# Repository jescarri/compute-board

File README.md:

# compute-board

This project is part of a template ecosystem for generating add-ons for my
custom esp32-powered compute boards.

It expects a 4-layer PCB with controlled impedance to 50 ohms.

<!-- KICAD_CI:START - Do not edit; auto-generated by .github/workflows/kicad-ci.yml -->

### Board preview

| Top | Bottom |
|---|---|
|  |  |

- [Schematic (PDF)](https://jescarri.github.io/compute-board/main/schematic/)
- [PCB layers (PDF)](https://jescarri.github.io/compute-board/main/pcb/)
- [STEP file](https://jescarri.github.io/compute-board/main/)
- [Full preview site](https://jescarri.github.io/compute-board/main/)

_Last updated from commit `0503de4` on 2026-06-19._
<!-- KICAD_CI:END -->

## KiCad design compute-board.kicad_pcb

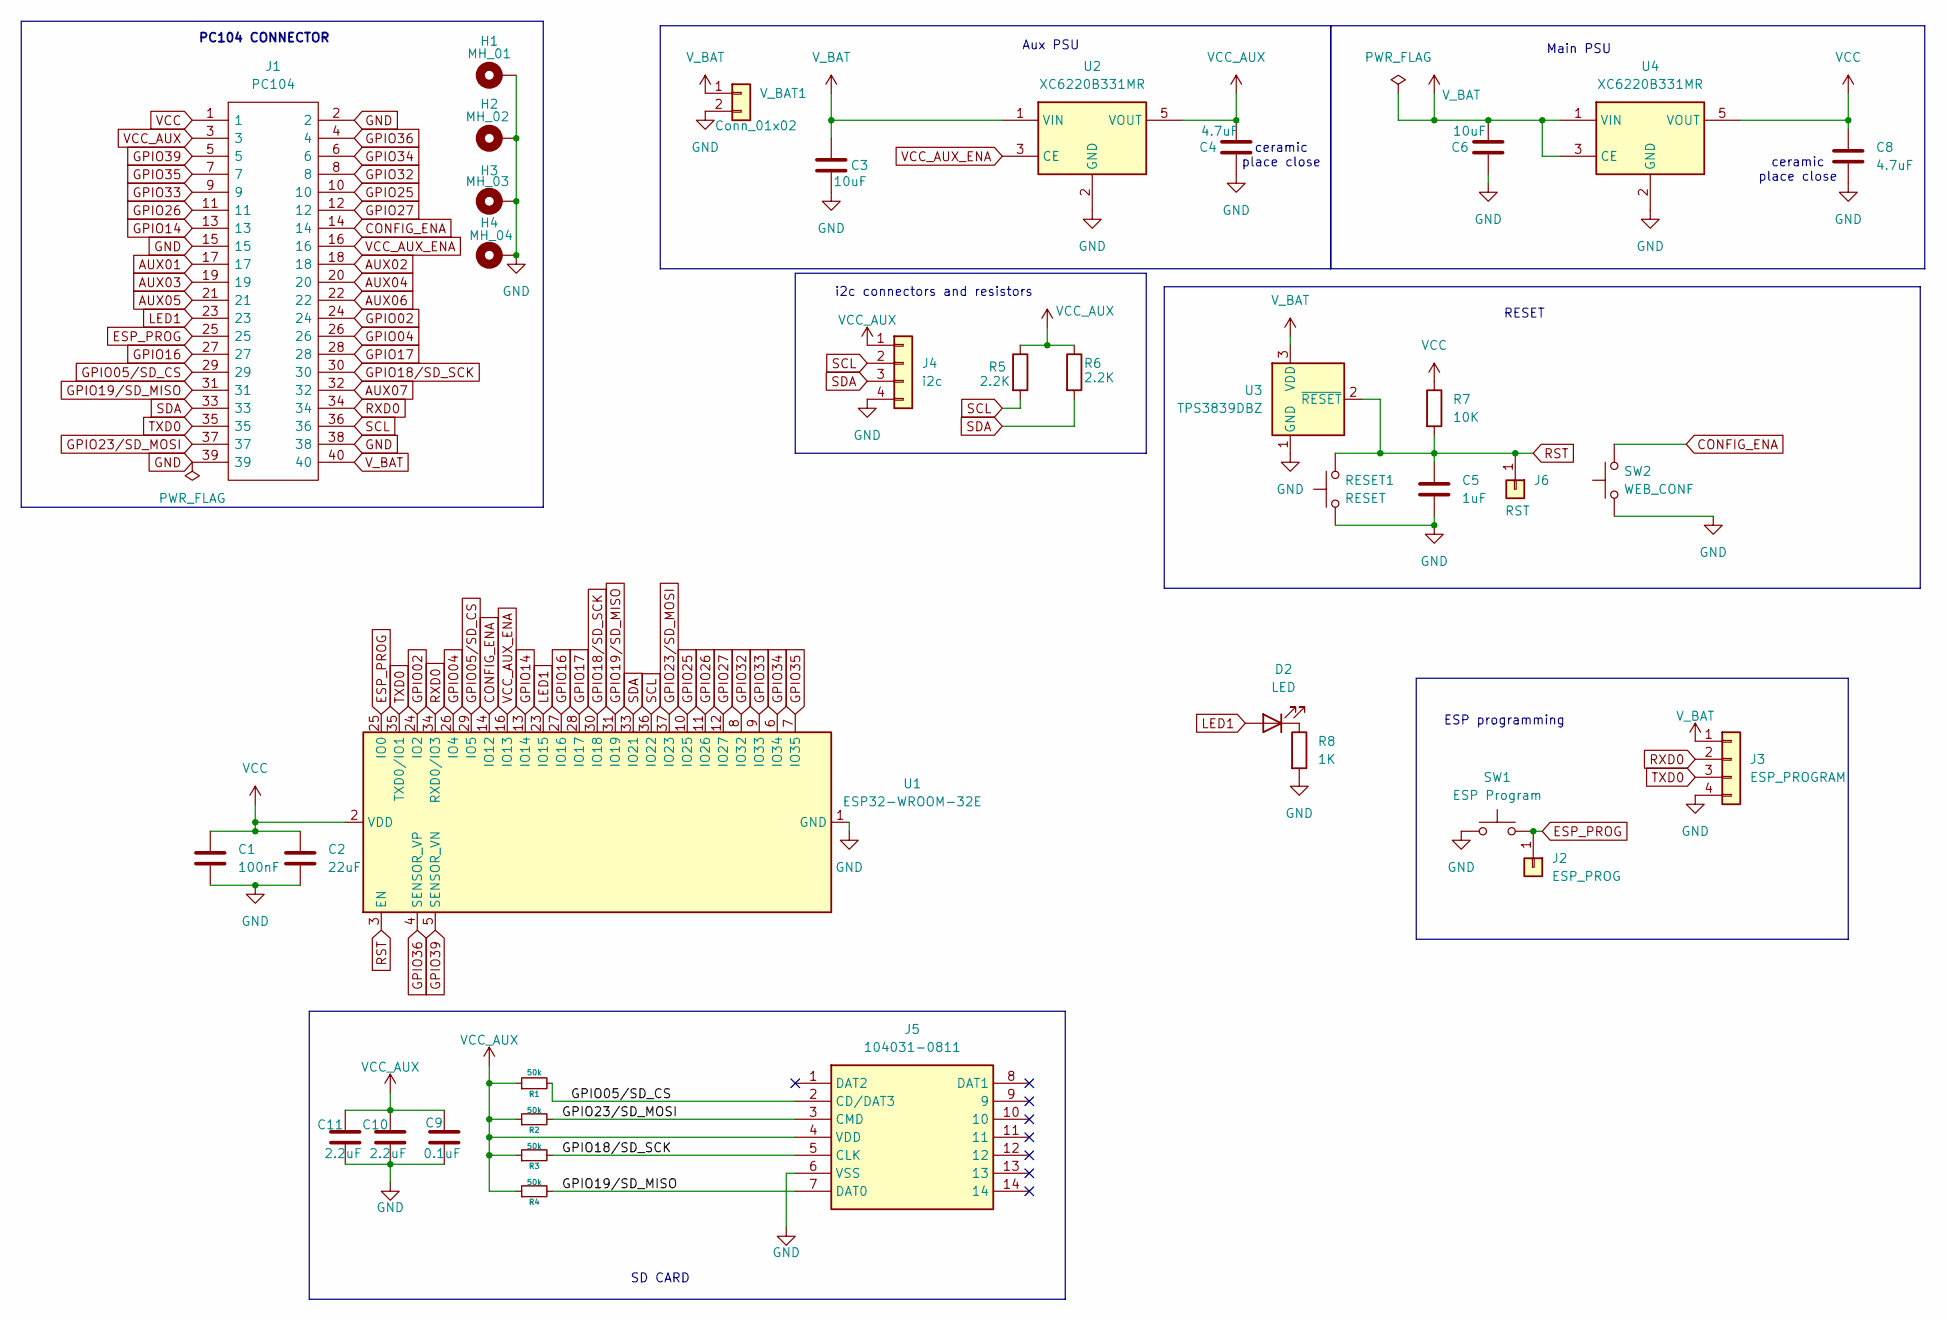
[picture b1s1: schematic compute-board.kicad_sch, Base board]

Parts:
C1: 100nF; C_1206_3216Metric_Pad1.33x1.80mm_HandSolder
C2: 22uF; CP_EIA-3528-21_Kemet-B_HandSolder
C3, C6: 10uF; C_1206_3216Metric_Pad1.33x1.80mm_HandSolder
C4, C8: 4.7uF; C_1206_3216Metric_Pad1.33x1.80mm_HandSolder
C5: 1uF; C_1206_3216Metric_Pad1.33x1.80mm_HandSolder
C9: 0.1uF; C_1206_3216Metric_Pad1.33x1.80mm_HandSolder
C10, C11: 2.2uF; C_1206_3216Metric_Pad1.33x1.80mm_HandSolder
D2: LED; LED_0603_1608Metric_Pad1.05x0.95mm_HandSolder
H1: MH_01; MountingHole_3.2mm_M3_ISO7380_Pad_TopBottom
H2: MH_02; MountingHole_3.2mm_M3_ISO7380_Pad_TopBottom
H3: MH_03; MountingHole_3.2mm_M3_ISO7380_Pad_TopBottom
H4: MH_04; MountingHole_3.2mm_M3_ISO7380_Pad_TopBottom
J1: PC104; RHDR40W66P254_2X20_5146X500X1105P; Manufacturer_Part_Number M20-6102045; Mouser Part Number 855-M20-6102045
J2: ESP_PROG; TestPoint_Pad_2.0x2.0mm
J3: ESP_PROGRAM; JST_XH_B4B-XH-AM_1x04_P2.50mm_Vertical
J4: i2c; JST_XH_B4B-XH-AM_1x04_P2.50mm_Vertical
J5: 104031-0811; 1040310811; Mouser Part Number 538-104031-0811
J6: RST; TestPoint_Pad_2.0x2.0mm
R1, R2, R3, R4: 50k; R_1206_3216Metric_Pad1.30x1.75mm_HandSolder
R5, R6: 2.2K; R_1206_3216Metric_Pad1.30x1.75mm_HandSolder
R7: 10K; R_1206_3216Metric_Pad1.30x1.75mm_HandSolder
R8: 1K; R_1206_3216Metric_Pad1.30x1.75mm_HandSolder
RESET1: RESET; SW_Push_1P1T_XKB_TS-1187A
SW1: ESP Program; SW_Push_1P1T_XKB_TS-1187A
SW2: WEB_CONF; SW_Push_1P1T_XKB_TS-1187A
U1: ESP32-WROOM-32E; ESP32-WROOM-32D
U2, U4: XC6220B331MR; SOT-23-5
U3: TPS3839DBZ; SOT-23
V_BAT1: Conn_01x02; Altech_AK300_1x02_P5.00mm_45-Degree

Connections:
AUX01: J1.17
AUX02: J1.18
AUX03: J1.19
AUX04: J1.20
AUX05: J1.21
AUX06: J1.22
AUX07: J1.32
CONFIG_ENA: J1.14, SW2.2, U1.14 (IO12)
ESP_PROG: J1.25, J2.1, SW1.2, U1.25 (IO0)
GND: C1.2, C2.2, C3.1, C4.2, C5.2, C6.2, C8.2, C9.2, C10.2, C11.2, H1.1, H2.1, H3.1, H4.1, J1.2, J1.15, J1.38, J1.39, J3.4, J4.4, J5.6 (VSS), R8.2, RESET1.1, SW1.1, SW2.1, U1.1 (GND), U1.15 (GND), U1.38 (GND), U1.39 (GND), U2.2 (GND), U3.1 (GND), U4.2 (GND), V_BAT1.2
GPIO02: J1.24, U1.24 (IO2)
GPIO04: J1.26, U1.26 (IO4)
GPIO05/SD_CS: J1.29, J5.2 (CD/DAT3), R1.2, U1.29 (IO5)
GPIO14: J1.13, U1.13 (IO14)
GPIO16: J1.27, U1.27 (IO16)
GPIO17: J1.28, U1.28 (IO17)
GPIO18/SD_SCK: J1.30, J5.5 (CLK), R3.2, U1.30 (IO18)
GPIO19/SD_MISO: J1.31, J5.7 (DAT0), R4.2, U1.31 (IO19)
GPIO23/SD_MOSI: J1.37, J5.3 (CMD), R2.2, U1.37 (IO23)
GPIO25: J1.10, U1.10 (IO25)
GPIO26: J1.11, U1.11 (IO26)
GPIO27: J1.12, U1.12 (IO27)
GPIO32: J1.8, U1.8 (IO32)
GPIO33: J1.9, U1.9 (IO33)
GPIO34: J1.6, U1.6 (IO34)
GPIO35: J1.7, U1.7 (IO35)
GPIO36: J1.4, U1.4 (SENSOR_VP)
GPIO39: J1.5, U1.5 (SENSOR_VN)
LED1: D2.2 (A), J1.23, U1.23 (IO15)
unnamed: D2.1 (K), R8.1
RST: C5.1, J6.1, R7.2, RESET1.2, U1.3 (EN), U3.2 (~RESET)
RXD0: J1.34, J3.2, U1.34 (RXD0/IO3)
SCL: J1.36, J4.2, R5.2, U1.36 (IO22)
SDA: J1.33, J4.3, R6.2, U1.33 (IO21)
TXD0: J1.35, J3.3, U1.35 (TXD0/IO1)
VCC: C1.1, C2.1, C8.1, J1.1, R7.1, U1.2 (VDD), U4.5 (VOUT)
VCC_AUX: C4.1, C9.1, C10.1, C11.1, J1.3, J4.1, J5.4 (VDD), R1.1, R2.1, R3.1, R4.1, R5.1, R6.1, U2.5 (VOUT)
VCC_AUX_ENA: J1.16, U1.16 (IO13), U2.3 (CE)
V_BAT: C3.2, C6.1, J1.40, J3.1, U2.1 (VIN), U3.3 (VDD), U4.1 (VIN), U4.3 (CE), V_BAT1.1

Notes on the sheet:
PC104 CONNECTOR
SD CARD
ceramic place close
ESP programming
Main PSU
RESET
Aux PSU
i2c connectors and resistors

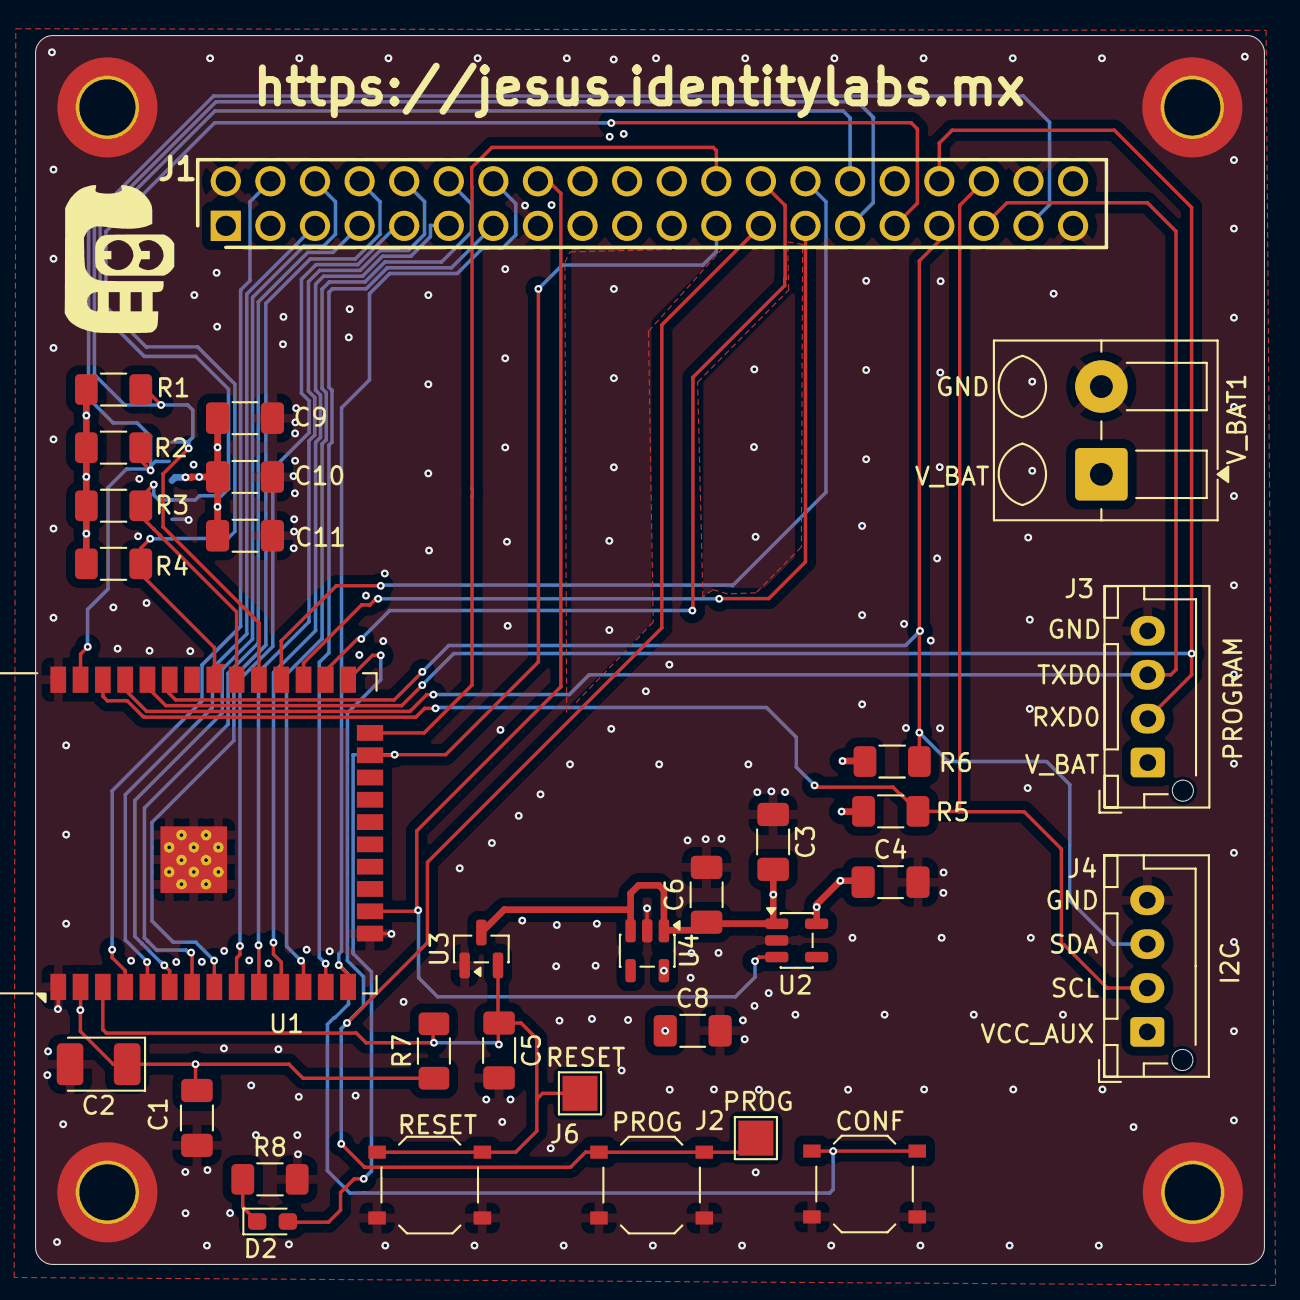
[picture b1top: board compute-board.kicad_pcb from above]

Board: 4 copper layers, 70.0 x 70.0 mm, 37 parts (1 on the bottom side), 32 nets.

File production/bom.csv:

Designator,Footprint,Quantity,Value,LCSC Part #
C1,1206,1,100nF,
"C10, C11",1206,2,2.2uF,
C2,CP_EIA-3528-21_Kemet-B_HandSolder,1,22uF,
"C3, C6",1206,2,10uF,
"C4, C8",1206,2,4.7uF,
"C5, C7",1206,2,1uF,
C9,1206,1,0.1uF,
D1,LED_WS2812B-2020_PLCC4_2.0x2.0mm,1,WS2812B-2020,
J1,RHDR40W66P254_2X20_5146X500X1105P,1,PC104,
J2,TestPoint_Pad_2.0x2.0mm,1,ESP_PROG,
J3,JST_XH_B4B-XH-AM_1x04_P2.50mm_Vertical,1,ESP_PROGRAM,
J4,JST_XH_B4B-XH-AM_1x04_P2.50mm_Vertical,1,i2c,
J5,1040310811,1,104031-0811,
J6,TestPoint_Pad_2.0x2.0mm,1,RST,
"R1, R2, R3, R4",1206,4,50k,
"R5, R6",1206,2,2.2K,
"R7, R8",1206,2,10K,
RESET1,SW_Push_1P1T_XKB_TS-1187A,1,RESET,
SW1,SW_Push_1P1T_XKB_TS-1187A,1,ESP Program,
SW2,SW_Push_1P1T_XKB_TS-1187A,1,WEB_CONF,
U1,ESP32-WROOM-32D,1,ESP32-WROOM-32E,
"U2, U4",SOT-23-5,2,XC6220B331MR,
U3,SOT-23,1,TPS3839DBZ,
V_BAT1,Altech_AK300_1x02_P5.00mm_45-Degree,1,Conn_01x02,

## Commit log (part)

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2026-04-09 ADD: computeboard picture
2026-04-09 FIX: gitignore and delete backups
2026-04-10 ci: publish pr-1/838e1fd6d3c0c0f1599182fbb91cea15f4f98616 from bdcb9487d25f2a9be767d5cc476c655ca484be29 bdcb9487d25f2a9be767d5cc476c655ca484be29
2026-04-10 FIX: routing recommendations
2026-04-10 ADD: claude.md
2026-04-10 ci: publish pr-1/c6535da22cec538a9f9930267ff61dc2ed08183c from 7356c10ba3ea037635d8e9efe8061dd1c41ed830 7356c10ba3ea037635d8e9efe8061dd1c41ed830
2026-04-10 ci: publish pr-1/b4c1ac4ad0eaaceb5562346a43c9505d27391aab from 3f1d120cc33d3e62664f2c24a0807448a388b286 3f1d120cc33d3e62664f2c24a0807448a388b286
2026-04-10 ci: publish pr-1/a5dd1f6a5ab4f98825923cf4780d62729f225bf2 from 03103d1f6b266c53c0fb182fe1da3f26f942c9b4 03103d1f6b266c53c0fb182fe1da3f26f942c9b4
2026-04-10 ci: publish pr-1/bda65897c5462826341dab371d24fc449d527cb3 from b9ce3580a86a79957b9247efa2499308b020842c b9ce3580a86a79957b9247efa2499308b020842c
2026-04-10 ci: publish pr-1/569edc01536798c60979d32e18ac6029e771eff1 from 81cc384ae9abc874f944a2216064a2213cd803a8 81cc384ae9abc874f944a2216064a2213cd803a8
2026-04-10 ci: refresh landing index
2026-04-10 ci: publish pr-1/60661b45dbc769d1a3295fa39b8ca982458c22ea from 194e99a27b99de5b87d5035e184e61a899eca27f 194e99a27b99de5b87d5035e184e61a899eca27f
2026-04-10 UPDATE: schematic and pcb revision
2026-04-10 ci: publish pr-1/b336f07a6228bbbd52a65cdc73c2222e07f3b47c from 194ca90a44298955533c5c7c293652f1daca2e28 194ca90a44298955533c5c7c293652f1daca2e28
2026-04-10 FIX: bottom skilscreen
2026-04-10 ci: publish pr-1/b1c7e16424a233b4d73892ca29eb828ac7e10e82 from 633f21e397466ad70819ac2017b3226f6141d070 633f21e397466ad70819ac2017b3226f6141d070
2026-04-10 ci: remove preview for PR #1
2026-04-10 ci: publish main from 20183833f2d57a8877904b8cd1f8b67eb847626b 20183833f2d57a8877904b8cd1f8b67eb847626b
2026-04-10 docs(readme): update CI preview [skip ci]
2026-04-10 ci: publish pr-2/62658bf4cfa2ef1732cf9209b66e9144192023a6 from 4f5c837c5c32c02317255c3c1307122695fb192c 4f5c837c5c32c02317255c3c1307122695fb192c
2026-05-28 ci: publish pr-3/3057eec6464144fc787b269f9a99a64fd15de04e from da72bc3eb212c5dda0d8cbed5f74501ab0e53239 da72bc3eb212c5dda0d8cbed5f74501ab0e53239
2026-05-28 ci: publish main from 8980b51a8a1b4039bcc72ec4f87a5f76b3dd275a 8980b51a8a1b4039bcc72ec4f87a5f76b3dd275a
2026-06-19 ADD: bom
2026-06-19 ci: publish main from 0503de4c3c16543574e7465c92381d9863c14760 0503de4c3c16543574e7465c92381d9863c14760
